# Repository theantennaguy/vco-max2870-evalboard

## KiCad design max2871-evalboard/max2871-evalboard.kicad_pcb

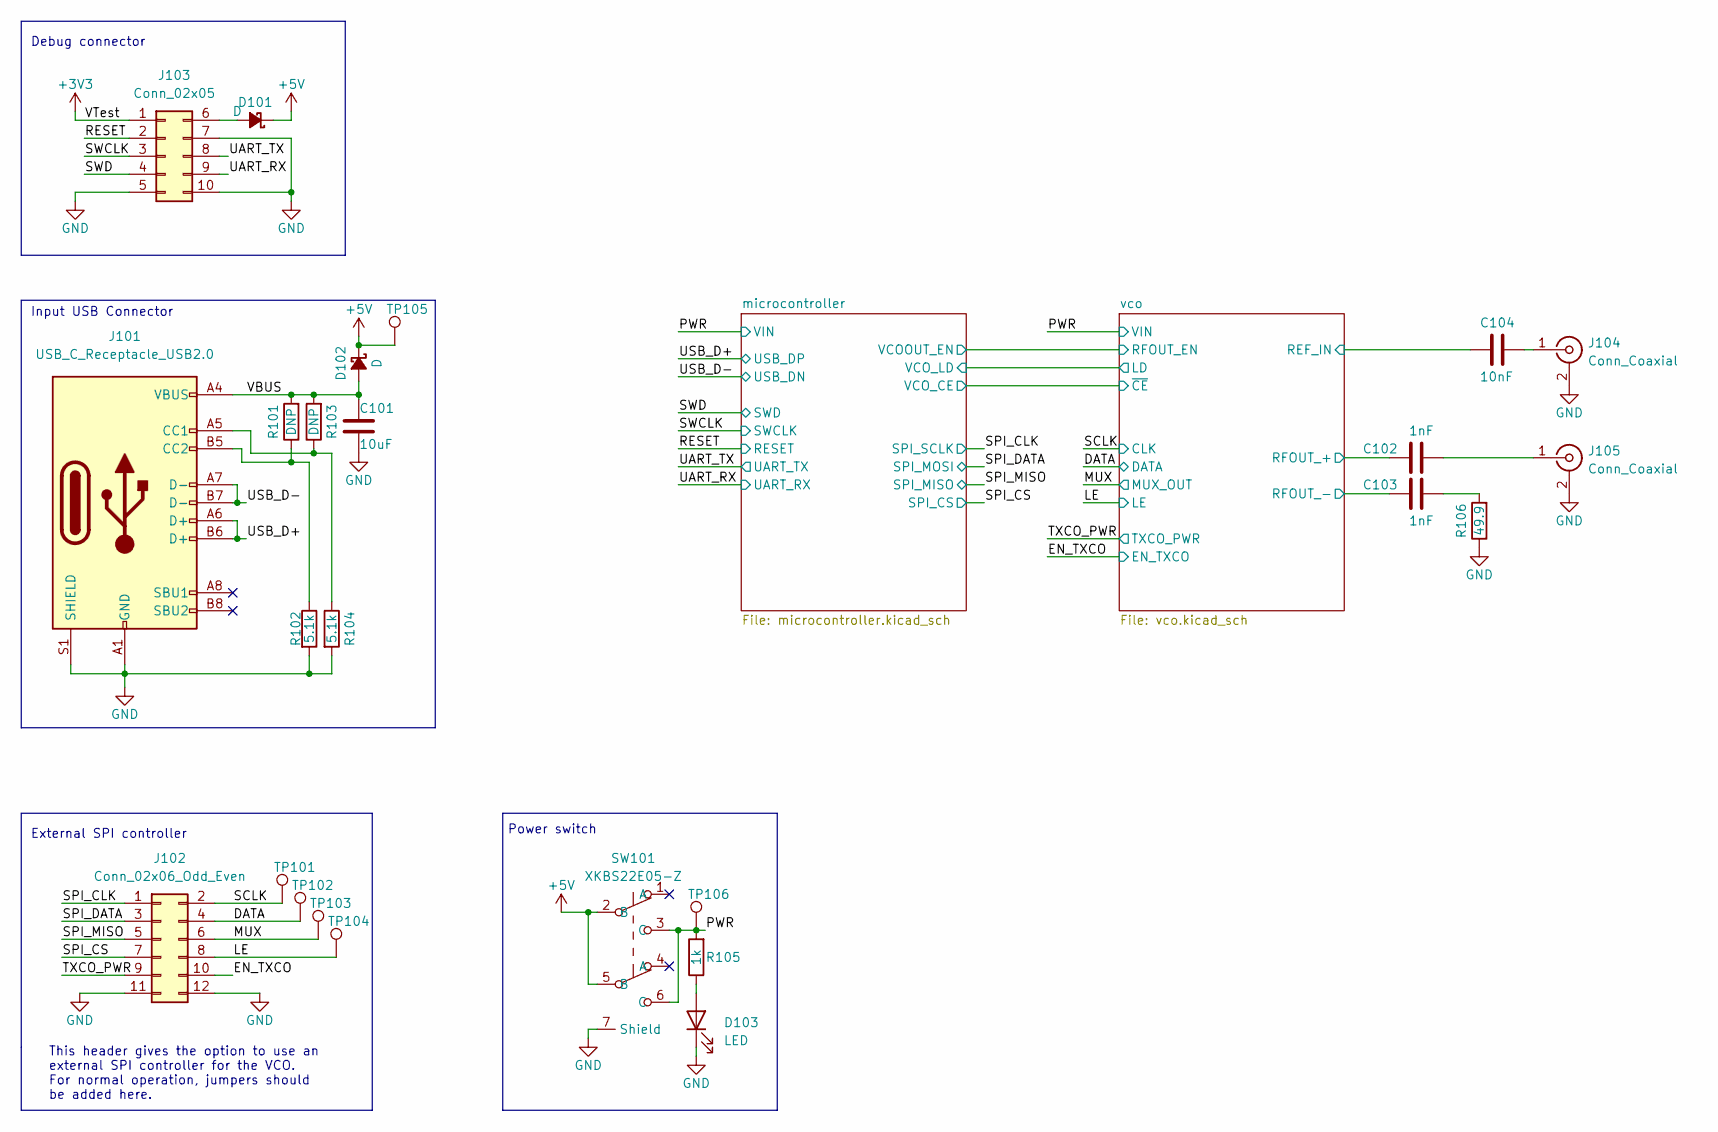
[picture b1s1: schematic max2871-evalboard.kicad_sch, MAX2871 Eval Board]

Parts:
C101: 10uF; C_0603_1608Metric; Part Number CL10A106MO8NQNC; LCSC C92487
C102, C103: 1nF; C_0402_1005Metric; Part Number GCM155R71H102KA37D; LCSC C126532
C104: 10nF; C_0402_1005Metric; Part Number TMK105B7103KVHF; LCSC C650944
D101, D102: D; D_SMA; Part Number SS12; LCSC C2898535
D103: LED; LED_D3.0mm_Horizontal_O3.81mm_Z2.0mm
J101: USB_C_Receptacle_USB2.0; GCT_USB4105-GF-A; Part Number USB4105-GF-A
J102: Conn_02x06_Odd_Even; PinHeader_2x06_P2.54mm_Horizontal; Part Number PZ254R-12-12P; LCSC C492434
J103: Conn_02x05; PinHeader_2x05_P1.27mm_Vertical
J104, J105: Conn_Coaxial; LINX_CONSMA002-L; Part Number DOSIN-806-0186; LCSC C709668
R101, R103: DNP; R_0402_1005Metric
R102, R104: 5.1k; R_0402_1005Metric; Part Number PTFR0402B5K10N9; LCSC C351692
R105: 1k; R_0402_1005Metric; Part Number RT0402CRE071KL; LCSC C705665
R106: 49.9; R_0402_1005Metric; Part Number PTFR0402B49R9N9; LCSC C2692754
SW101: XKBS22E05-Z; Part Number XKBS22E05-Z; LCSC C692489
TP101, TP102, TP103, TP104: TestPoint_Pad_D1.0mm
TP105, TP106: TestPoint_Pad_D1.5mm

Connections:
+3V3: J103.1; also elsewhere on the board
+5V: D101.1 (K), D102.1 (K), SW101.2 (B), SW101.5 (B), TP105.1
/DATA: J102.4, TP102.1; also elsewhere on the board
/EN_TXCO: J102.10; also elsewhere on the board
/LE: J102.8, TP104.1; also elsewhere on the board
/MUX: J102.6, TP103.1; also elsewhere on the board
/PWR: R105.2, SW101.3 (C), SW101.6 (C), TP106.1; also elsewhere on the board
/RESET: J103.2; also elsewhere on the board
/SCLK: J102.2, TP101.1; also elsewhere on the board
/SPI_CLK: J102.1; also elsewhere on the board
/SPI_CS: J102.7; also elsewhere on the board
/SPI_DATA: J102.3; also elsewhere on the board
/SPI_MISO: J102.5; also elsewhere on the board
/SWCLK: J103.3; also elsewhere on the board
/SWD: J103.4; also elsewhere on the board
/TXCO_PWR: J102.9; also elsewhere on the board
/UART_RX: J103.9; also elsewhere on the board
/UART_TX: J103.8; also elsewhere on the board
/USB_D+: J101.A6 (D+), J101.B6 (D+); also elsewhere on the board
/USB_D-: J101.A7 (D-), J101.B7 (D-); also elsewhere on the board
/VBUS: C101.1, D102.2 (A), J101.A4 (VBUS), J101.A9 (VBUS), J101.B4 (VBUS), J101.B9 (VBUS), R101.2, R103.2
/vco/REF_CLK: C104.2; also elsewhere on the board
/vco/RFOUT_N: C103.1; also elsewhere on the board
/vco/RFOUT_P: C102.1; also elsewhere on the board
GND: C101.2, D103.1 (K), J101.A1 (GND), J101.A12 (GND), J101.B1 (GND), J101.B12 (GND), J101.S1 (SHIELD), J102.11, J102.12, J103.5, J103.7, J103.10, J104.2 (Ext), J105.2 (Ext), R102.2, R104.2, R106.1, SW101.7 (Shield); also elsewhere on the board
unnamed: C102.2, J105.1 (In)
unnamed: C103.2, R106.2
unnamed: C104.1, J104.1 (In)
unnamed: D101.2 (A), J103.6
unnamed: D103.2 (A), R105.1
unnamed: J101.A5 (CC1), R103.1, R104.1
unnamed: J101.B5 (CC2), R101.1, R102.1

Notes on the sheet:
Input USB Connector
Power switch
Debug connector
This header gives the option to use an external SPI controller for the VCO. For normal operation, jumpers should be added here.
External SPI controller

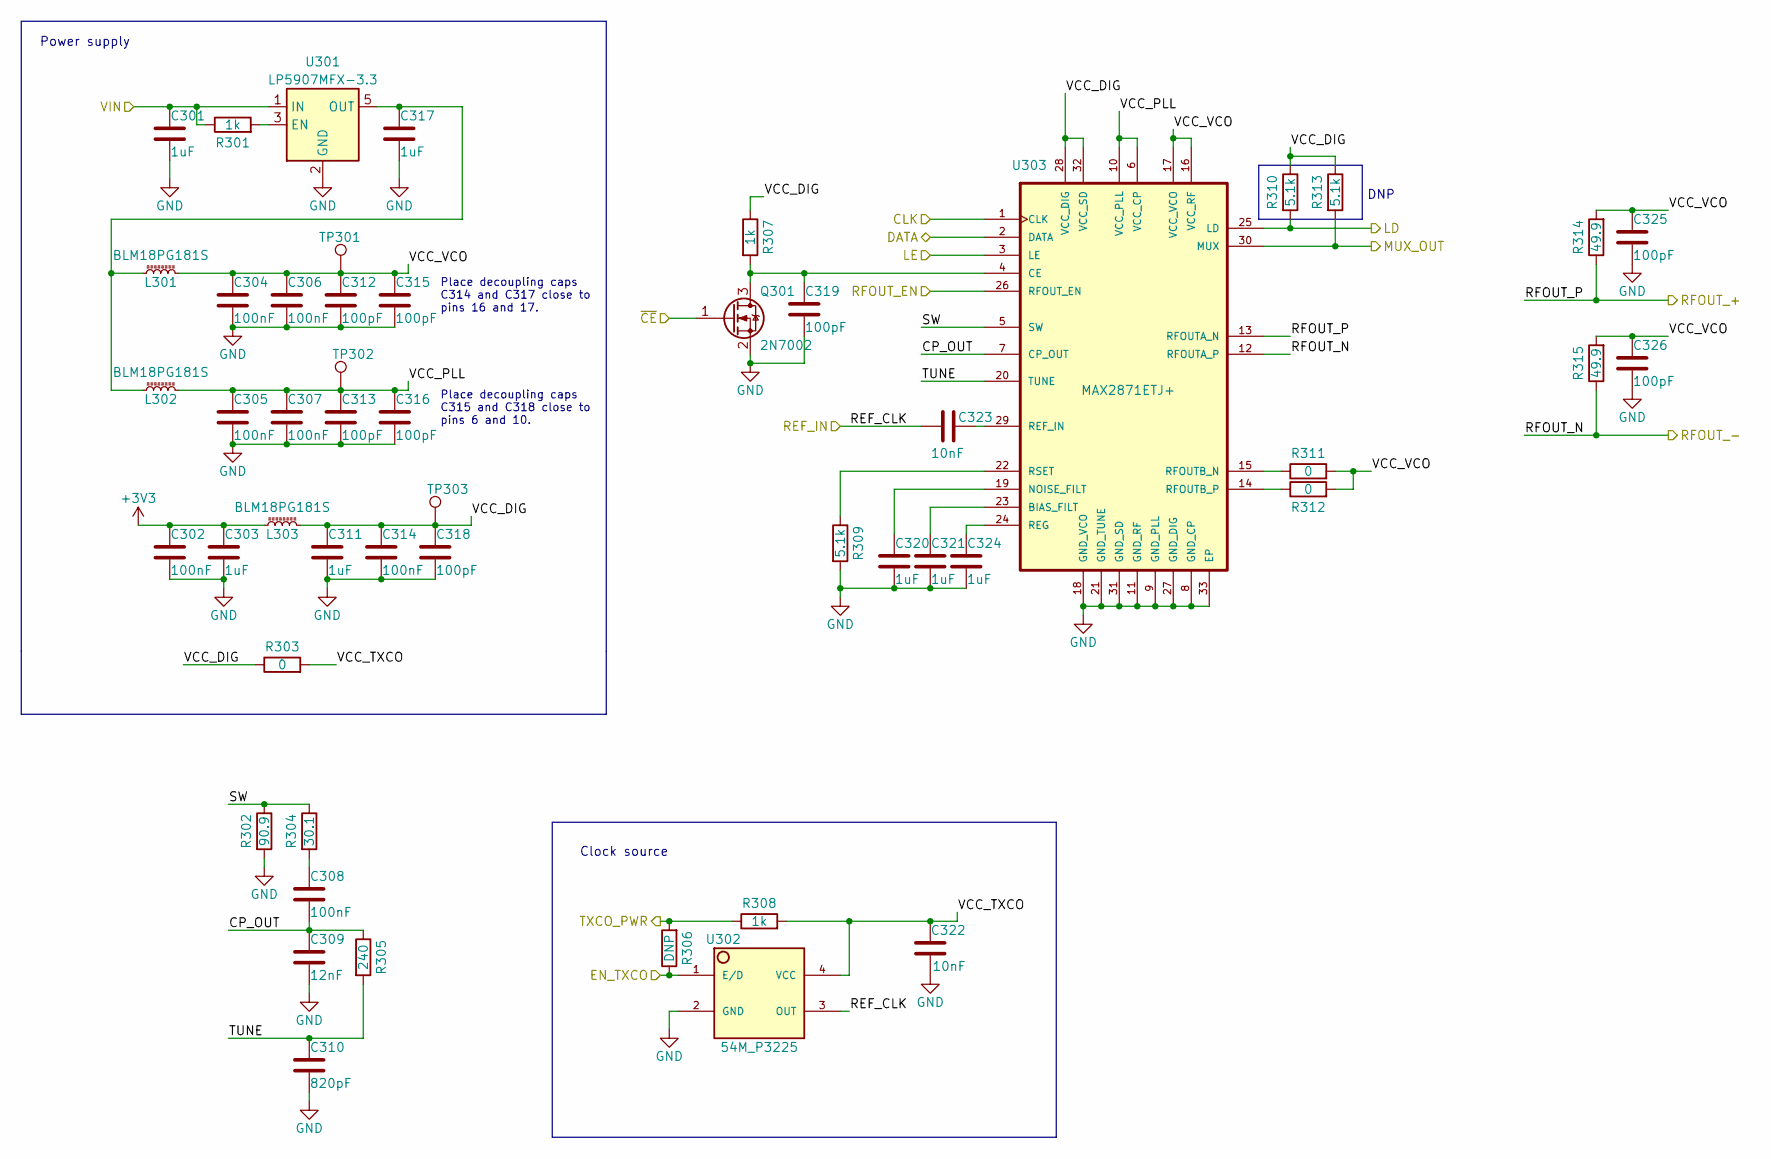
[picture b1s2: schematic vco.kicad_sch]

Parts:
C301, C303, C311, C317, C320, C321, C324: 1uF; C_0402_1005Metric; Part Number GCM155C71A105KE38D; LCSC C126521
C302, C304, C305, C306, C307, C308, C314: 100nF; C_0402_1005Metric; Part Number CL05F104ZO5NNNC; LCSC C84701
C309: 12nF; C_0402_1005Metric; Part Number CC0402KRX7R8BB123; LCSC C113786
C310: 820pF; C_0402_1005Metric; Part Number CC0402KRX7R9BB821; LCSC C107031
C312, C313, C315, C316, C318, C319, C325, C326: 100pF; C_0402_1005Metric; Part Number CC0402KRX7R7BB101; LCSC C541374
C322, C323: 10nF; C_0402_1005Metric; Part Number TMK105B7103KVHF; LCSC C650944
L301, L302, L303: BLM18PG181S; L_0603_1608Metric; Part Number BLM18PG181SH1D; LCSC C710383
Q301: 2N7002; SOT-23; Part Number 2N7002; LCSC C389059
R301, R307, R308: 1k; R_0402_1005Metric; Part Number RT0402CRE071KL; LCSC C705665
R302: 90.9; R_0402_1005Metric; Part Number RT0402BRD0790R9L; LCSC C852950
R303, R311, R312: 0; R_0402_1005Metric; Part Number PA0402-R-070RL; LCSC C4044221
R304: 30.1; R_0402_1005Metric; Part Number PTFR0402B49R9N9; LCSC C2692754
R305: 240; R_0402_1005Metric; Part Number PTFR0402B49R9N9; LCSC C2692754
R306: DNP; R_0603_1608Metric
R309, R310, R313: 5.1k; R_0402_1005Metric; Part Number PTFR0402B5K10N9; LCSC C351692
R314, R315: 49.9; R_0402_1005Metric; Part Number PTFR0402B49R9N9; LCSC C2692754
TP301, TP302, TP303: TestPoint_Pad_D1.5mm
U301: LP5907MFX-3.3; SOT-23-5; Part Number LP5907QMFX-3.3Q1; LCSC C130005
U302: 54M_P3225; Crystal_SMD_3225-4Pin_3.2x2.5mm; Part Number O3254000153350; LCSC C437135
U303: MAX2871ETJ+; QFN50P500X500X80-33N; Partnumber MAX2871ETJ+

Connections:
+3V3: C302.1, C303.1, L303.1; also elsewhere on the board
/DATA: U303.2 (DATA); also elsewhere on the board
/EN_TXCO: R306.1, U302.1 (E/D); also elsewhere on the board
/LE: U303.3 (LE); also elsewhere on the board
/MUX: R313.2, U303.30 (MUX); also elsewhere on the board
/PWR: C301.1, R301.1, U301.1 (IN); also elsewhere on the board
/SCLK: U303.1 (CLK); also elsewhere on the board
/TXCO_PWR: R306.2, R308.1; also elsewhere on the board
/microcontroller/VCOOUT_EN: U303.26 (RFOUT_EN); also elsewhere on the board
/microcontroller/VCO_CE: Q301.1 (G); also elsewhere on the board
/microcontroller/VCO_LD: R310.2, U303.25 (LD); also elsewhere on the board
/vco/CP_OUT: C308.2, C309.1, R305.1, U303.7 (CP_OUT)
/vco/REF_CLK: C323.2, U302.3 (OUT); also elsewhere on the board
/vco/RFOUT_N: R315.1, U303.12 (RFOUTA_P); also elsewhere on the board
/vco/RFOUT_P: R314.1, U303.13 (RFOUTA_N); also elsewhere on the board
/vco/SW: R302.1, R304.1, U303.5 (SW)
/vco/TUNE: C310.1, R305.2, U303.20 (TUNE)
/vco/VCC_DIG: C311.1, C314.1, C318.1, L303.2, R303.1, R307.1, R310.1, R313.1, TP303.1, U303.28 (VCC_DIG), U303.32 (VCC_SD)
/vco/VCC_PLL: C305.1, C307.1, C313.1, C316.1, L302.2, TP302.1, U303.6 (VCC_CP), U303.10 (VCC_PLL)
/vco/VCC_TXCO: C322.2, R303.2, R308.2, U302.4 (VCC)
/vco/VCC_VCO: C304.1, C306.1, C312.1, C315.1, C325.1, C326.1, L301.2, R311.2, R312.2, R314.2, R315.2, TP301.1, U303.16 (VCC_RF), U303.17 (VCC_VCO)
GND: C301.2, C302.2, C303.2, C304.2, C305.2, C306.2, C307.2, C309.2, C310.2, C311.2, C312.2, C313.2, C314.2, C315.2, C316.2, C317.2, C318.2, C319.2, C320.2, C321.2, C322.1, C324.2, C325.2, C326.2, Q301.2 (S), R302.2, R309.2, U301.2 (GND), U302.2 (GND), U303.8 (GND_CP), U303.9 (GND_PLL), U303.11 (GND_RF), U303.18 (GND_VCO), U303.21 (GND_TUNE), U303.27 (GND_DIG), U303.31 (GND_SD), U303.33 (EP); also elsewhere on the board
unnamed: C308.1, R304.2
unnamed: C317.1, L301.1, L302.1, U301.5 (OUT)
unnamed: C319.1, Q301.3 (D), R307.2, U303.4 (CE)
unnamed: C320.1, U303.19 (NOISE_FILT)
unnamed: C321.1, U303.23 (BIAS_FILT)
unnamed: C323.1, U303.29 (REF_IN)
unnamed: C324.1, U303.24 (REG)
unnamed: R301.2, U301.3 (EN)
unnamed: R309.1, U303.22 (RSET)
unnamed: R311.1, U303.15 (RFOUTB_N)
unnamed: R312.1, U303.14 (RFOUTB_P)

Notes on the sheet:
Clock source
Place decoupling caps C314 and C317 close to pins 16 and 17.
Power supply
DNP
Place decoupling caps C315 and C318 close to pins 6 and 10.

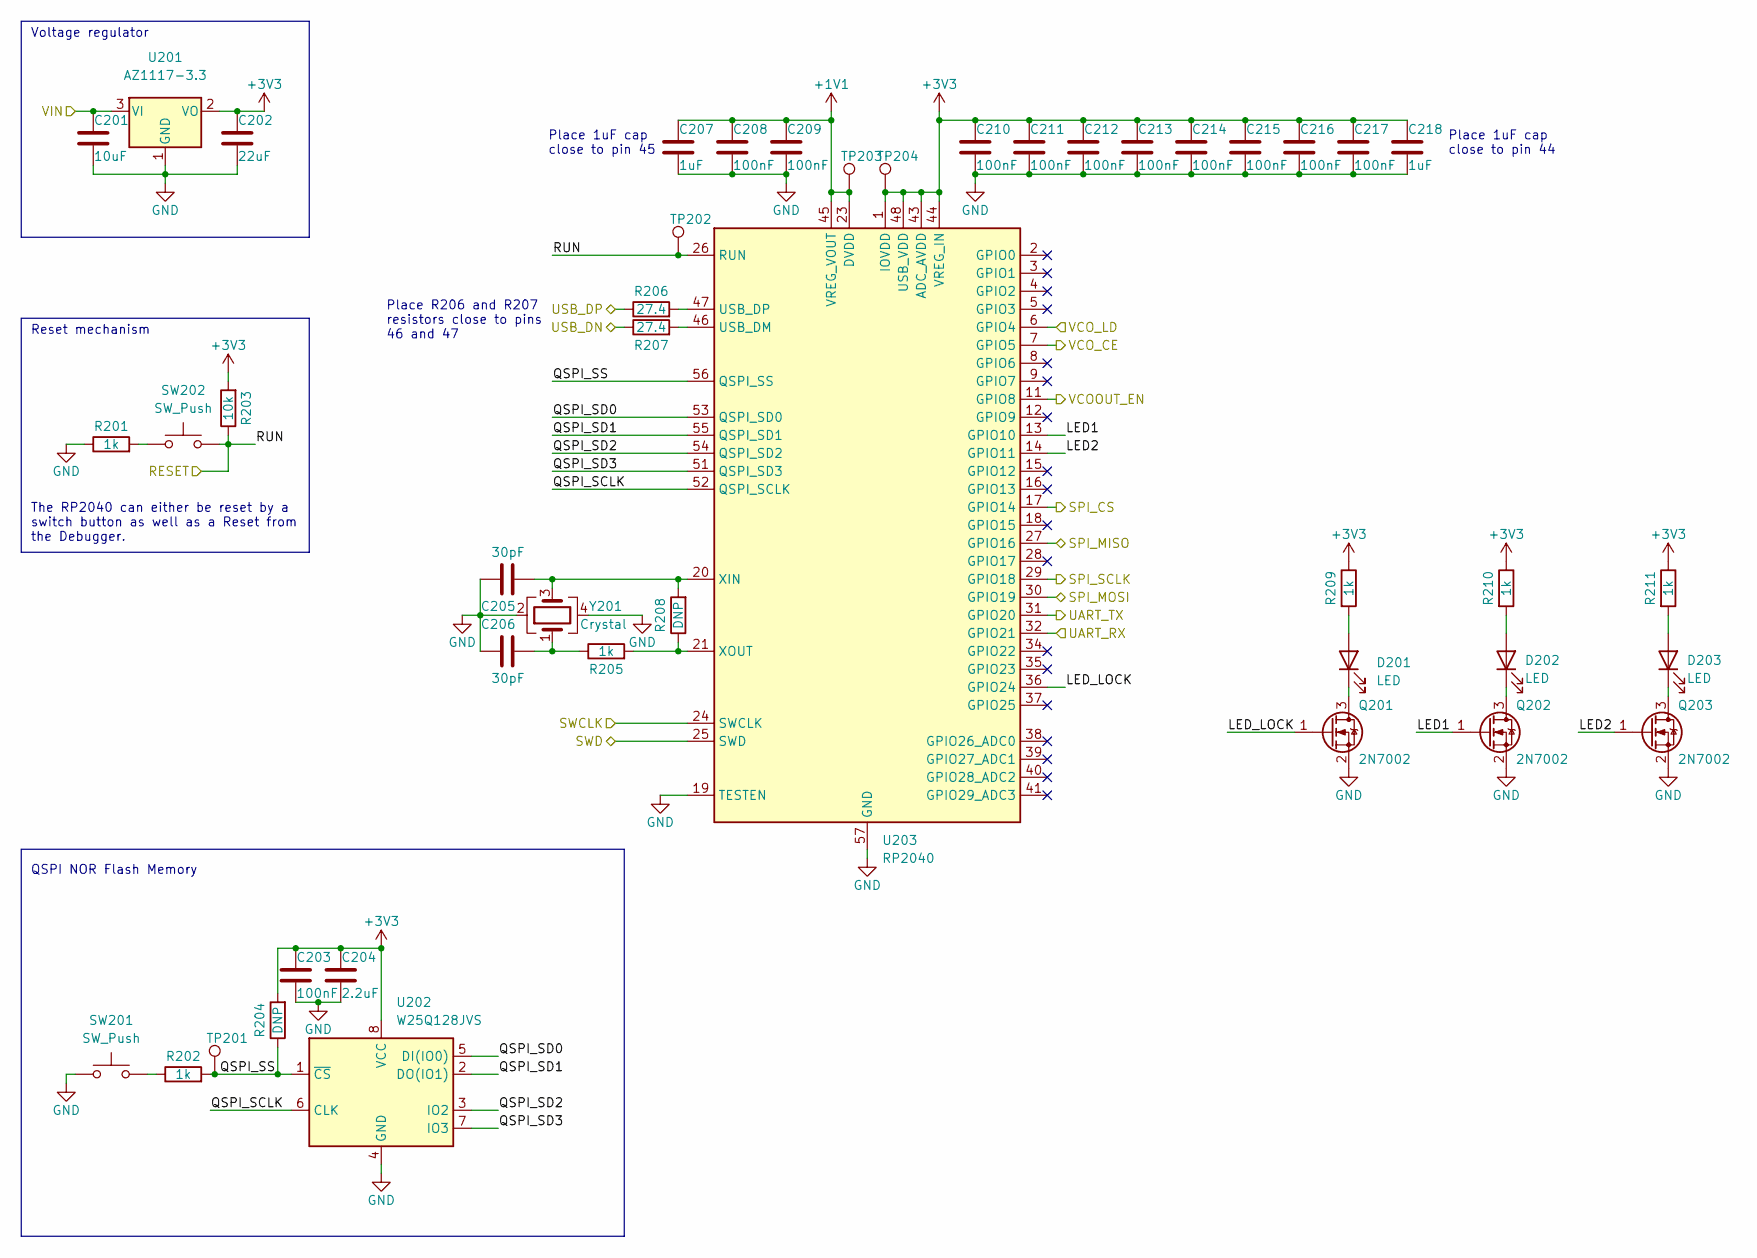
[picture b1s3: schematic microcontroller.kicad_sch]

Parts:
C201: 10uF; C_0603_1608Metric; Part Number CL10A106MO8NQNC; LCSC C92487
C202: 22uF; C_0805_2012Metric; Part Number CL21A226MAYNNNE; LCSC C602037
C203, C208, C209, C210, C211, C212, C213, C214, C215, C216, C217: 100nF; C_0402_1005Metric; Part Number CL05F104ZO5NNNC; LCSC C84701
C204: 2.2uF; C_0402_1005Metric; Part Number CL05F104ZO5NNNC; LCSC C84701
C205, C206: 30pF; C_0402_1005Metric; Part Number GCM1555C1H300JA16D; LCSC C161152
C207, C218: 1uF; C_0402_1005Metric; Part Number GCM155C71A105KE38D; LCSC C126521
D201: LED; LED_D3.0mm_Horizontal_O3.81mm_Z2.0mm
D202, D203: LED; LED_0603_1608Metric; Part Number 19-217/GHC-YR1S2/3T; LCSC C72043
Q201, Q202, Q203: 2N7002; SOT-23; Part Number 2N7002; LCSC C389059
R201, R202, R205, R209, R210, R211: 1k; R_0402_1005Metric; Part Number RT0402CRE071KL; LCSC C705665
R203: 10k; R_0402_1005Metric; Part Number RT0402BRC0710KL; LCSC C852428
R204, R208: DNP; R_0402_1005Metric
R206, R207: 27.4; R_0402_1005Metric; Part Number 0402WGF274JTCE; LCSC C31439
SW201, SW202: SW_Push; SW_TL3365AF180QG; Part Number TSA017A2540A03; LCSC C2888435
TP201, TP202, TP203, TP204: TestPoint_Pad_D1.5mm
U201: AZ1117-3.3; SOT-223-3_TabPin2; Part Number AZ1117H-3.3TRE1; LCSC C92517
U202: W25Q128JVS; SOIC-8_5.23x5.23mm_P1.27mm; Part Number W25Q128JVSIQ; LCSC C113767
U203: RP2040; QFN-56-1EP_7x7mm_P0.4mm_EP3.2x3.2mm; Part Number RP2040; LCSC C2040
Y201: Crystal; Crystal_SMD_3225-4Pin_3.2x2.5mm; Part Number TAXM12M4RLBDDT2T; LCSC C133334

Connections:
+1V1: C207.1, C208.1, C209.1, TP203.1, U203.23 (DVDD), U203.45 (VREG_VOUT), U203.50 (DVDD)
+3V3: C202.1, C203.1, C204.1, C210.1, C211.1, C212.1, C213.1, C214.1, C215.1, C216.1, C217.1, C218.1, R203.2, R204.2, R209.1, R210.1, R211.1, TP204.1, U201.2 (VO), U202.8 (VCC), U203.1 (IOVDD), U203.10 (IOVDD), U203.22 (IOVDD), U203.33 (IOVDD), U203.42 (IOVDD), U203.43 (ADC_AVDD), U203.44 (VREG_IN), U203.48 (USB_VDD), U203.49 (IOVDD); also elsewhere on the board
/PWR: C201.1, U201.3 (VI); also elsewhere on the board
/RESET: R203.1, SW202.2, TP202.1, U203.26 (RUN); also elsewhere on the board
/SPI_CLK: U203.29 (GPIO18); also elsewhere on the board
/SPI_CS: U203.17 (GPIO14); also elsewhere on the board
/SPI_DATA: U203.30 (GPIO19); also elsewhere on the board
/SPI_MISO: U203.27 (GPIO16); also elsewhere on the board
/SWCLK: U203.24 (SWCLK); also elsewhere on the board
/SWD: U203.25 (SWD); also elsewhere on the board
/UART_RX: U203.32 (GPIO21); also elsewhere on the board
/UART_TX: U203.31 (GPIO20); also elsewhere on the board
/USB_D+: R206.1; also elsewhere on the board
/USB_D-: R207.1; also elsewhere on the board
/microcontroller/LED1: Q202.1 (G), U203.13 (GPIO10)
/microcontroller/LED2: Q203.1 (G), U203.14 (GPIO11)
/microcontroller/LED_LOCK: Q201.1 (G), U203.36 (GPIO24)
/microcontroller/QSPI_SCLK: U202.6 (CLK), U203.52 (QSPI_SCLK)
/microcontroller/QSPI_SD0: U202.5 (DI(IO0)), U203.53 (QSPI_SD0)
/microcontroller/QSPI_SD1: U202.2 (DO(IO1)), U203.55 (QSPI_SD1)
/microcontroller/QSPI_SD2: U202.3 (IO2), U203.54 (QSPI_SD2)
/microcontroller/QSPI_SD3: U202.7 (IO3), U203.51 (QSPI_SD3)
/microcontroller/QSPI_SS: R202.2, R204.1, TP201.1, U202.1 (~CS), U203.56 (QSPI_SS)
/microcontroller/VCOOUT_EN: U203.11 (GPIO8); also elsewhere on the board
/microcontroller/VCO_CE: U203.7 (GPIO5); also elsewhere on the board
/microcontroller/VCO_LD: U203.6 (GPIO4); also elsewhere on the board
GND: C201.2, C202.2, C203.2, C204.2, C205.1, C206.1, C207.2, C208.2, C209.2, C210.2, C211.2, C212.2, C213.2, C214.2, C215.2, C216.2, C217.2, C218.2, Q201.2 (S), Q202.2 (S), Q203.2 (S), R201.1, SW201.1, U201.1 (GND), U202.4 (GND), U203.19 (TESTEN), U203.57 (GND), Y201.2, Y201.4; also elsewhere on the board
unnamed: C205.2, R208.2, U203.20 (XIN), Y201.3
unnamed: C206.2, R205.1, Y201.1
unnamed: D201.1 (K), Q201.3 (D)
unnamed: D201.2 (A), R209.2
unnamed: D202.1 (K), Q202.3 (D)
unnamed: D202.2 (A), R210.2
unnamed: D203.1 (K), Q203.3 (D)
unnamed: D203.2 (A), R211.2
unnamed 67: R201.2, SW202.1; also elsewhere on the board
unnamed 68: R202.1, SW201.2; also elsewhere on the board
unnamed: R205.2, R208.1, U203.21 (XOUT)
unnamed: R206.2, U203.47 (USB_DP)
unnamed: R207.2, U203.46 (USB_DM)

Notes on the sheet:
Place R206 and R207 resistors close to pins 46 and 47
The RP2040 can either be reset by a switch button as well as a Reset from the Debugger.
Place 1uF cap close to pin 45
Voltage regulator
Place 1uF cap close to pin 44
Reset mechanism
QSPI NOR Flash Memory

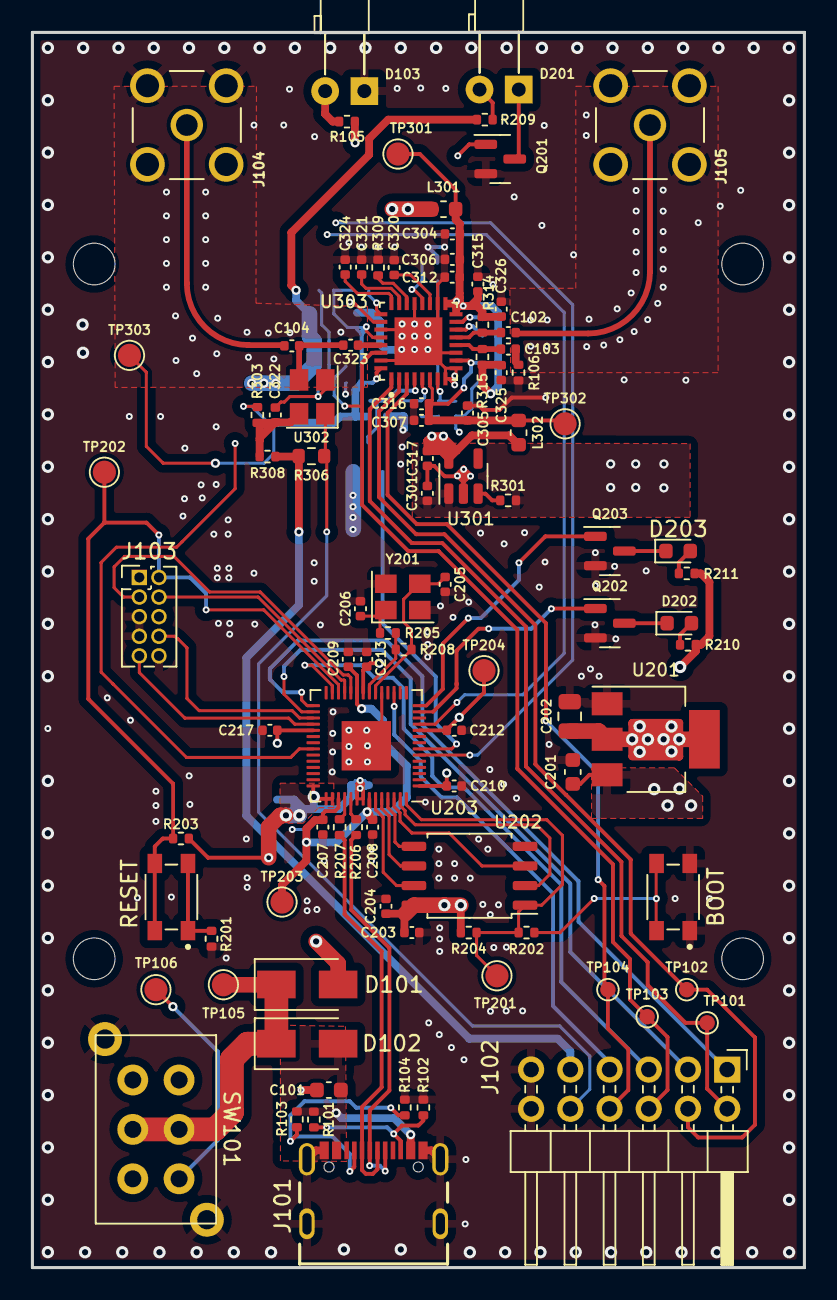
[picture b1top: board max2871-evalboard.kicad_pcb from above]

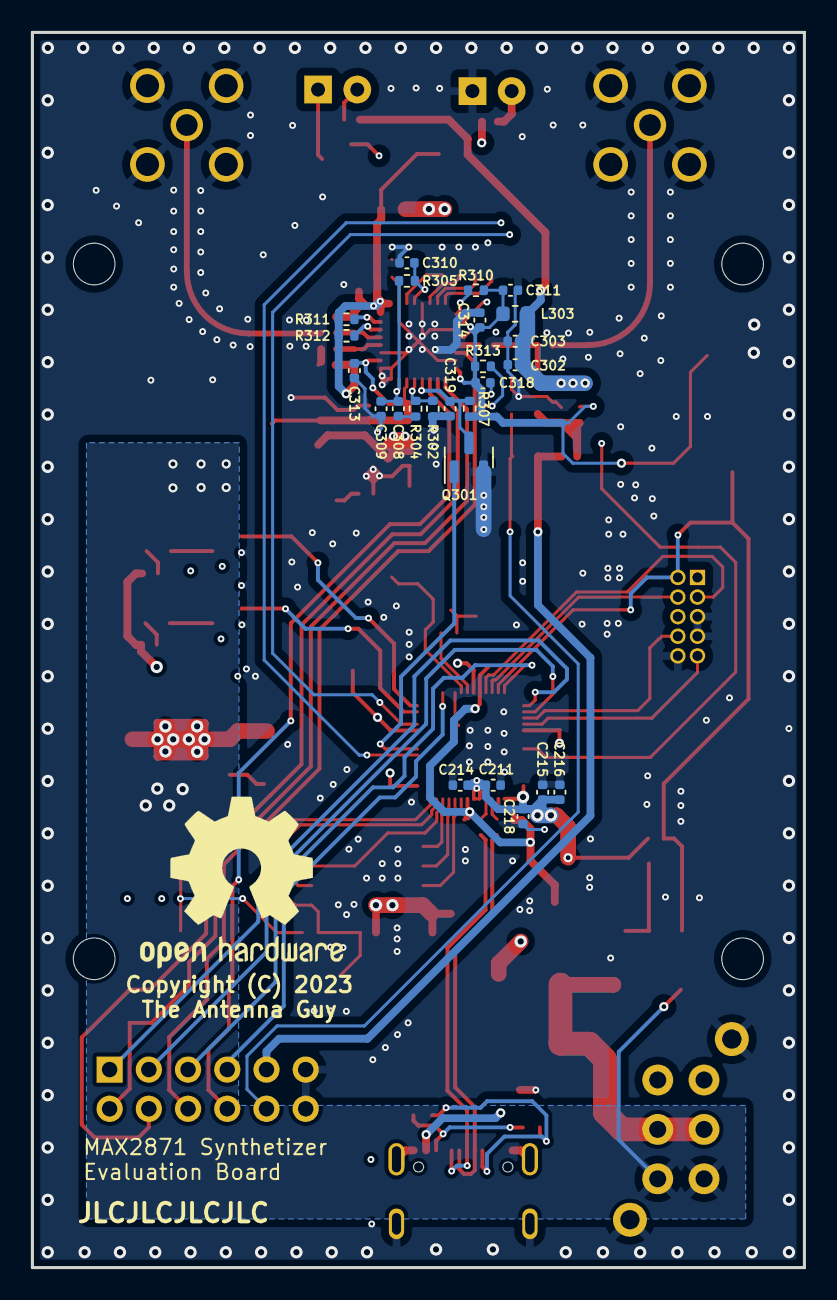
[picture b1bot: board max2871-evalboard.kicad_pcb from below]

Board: 4 copper layers, 50.0 x 80.0 mm, 121 parts (25 on the bottom side), 76 nets.

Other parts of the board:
BOOT: SW_Push; SW_TL3365AF180QG
RESET: SW_Push; SW_TL3365AF180QG

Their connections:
/RESET: RESET.2; also elsewhere on the board
GND: BOOT.1; also elsewhere on the board
unnamed 67: RESET.1; also elsewhere on the board
unnamed 68: BOOT.2; also elsewhere on the board

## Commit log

2022-11-28 Create_project and setup license
2022-11-28 Update project name
2022-12-02 Update Schematic
2022-12-05 Finish schematic - create PCB
2022-12-18 Finished schematics - started PCB design
2022-12-21 PCB placement complete
2022-12-26 Finish PCB design
2023-01-11 Finish layout design
2023-01-17 Finish PCB - generate fabrication files
2023-01-21 Update page layout

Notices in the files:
max2871-evalboard/max2871-evalboard.kicad_pcb:
Copyright (C) 2023
